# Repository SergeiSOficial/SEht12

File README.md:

# SEht12

That is 12 ethernet POE, I2C, CAN implementation. KiCAD source files

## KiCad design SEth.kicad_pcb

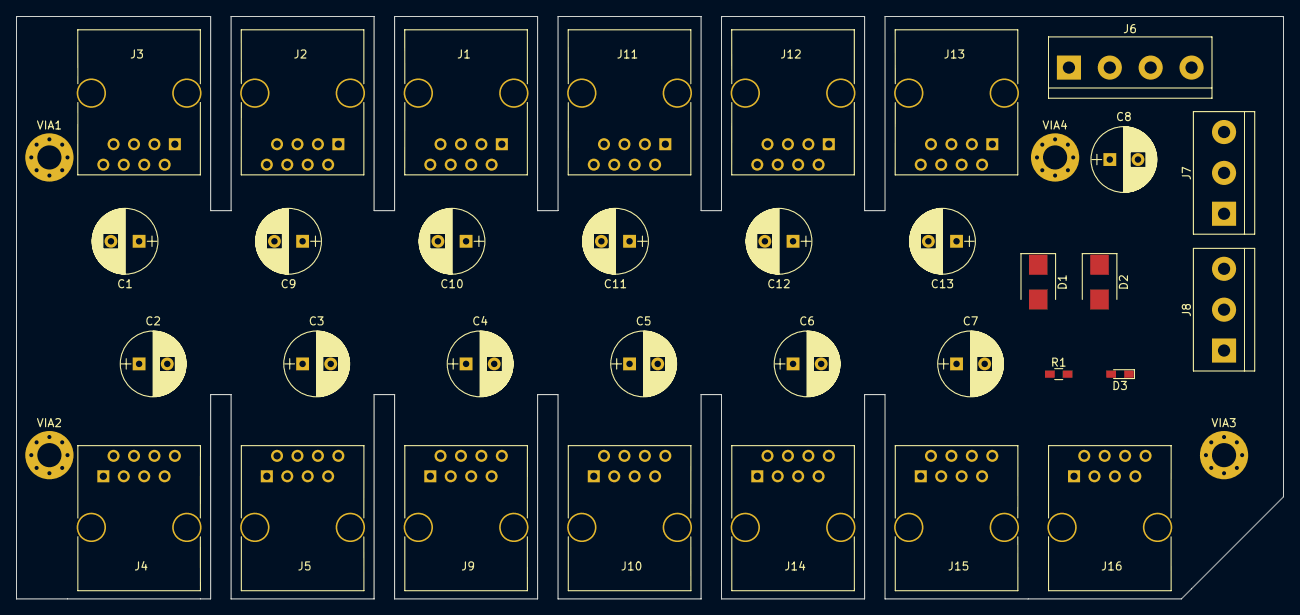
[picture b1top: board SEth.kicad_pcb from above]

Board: 2 copper layers, 157.5 x 72.4 mm, 37 parts (0 on the bottom side), 7 nets, no tracks yet.

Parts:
C1, C2, C3, C4, C5, C6, C7, C8, C9, C10, C11, C12, C13: CP; CP_Radial_D8.0mm_P3.50mm
D1: D_TVS; D_SMB
D2: D; D_SMB
D3: LED; LED_0603_HandSoldering
J1, J2, J3, J4, J5, J9, J10, J11, J12, J13, J14, J15, J16: RJ45; RJ45_8
J6: Screw_Terminal_01x04; TerminalBlock_bornier-4_P5.08mm
J7, J8: Screw_Terminal_01x03; TerminalBlock_bornier-3_P5.08mm
R1: 1K; R_0603_HandSoldering
VIA1, VIA2, VIA3, VIA4: 3mm_Pad_Via; MountingHole_3mm_Pad_Via

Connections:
+12V: C1.1, C2.1, C3.1, C4.1, C5.1, C6.1, C7.1, C8.1, C9.1, C10.1, C11.1, C12.1, C13.1, D1.1, D2.1, J1.4, J1.5, J2.4, J2.5, J3.4, J3.5, J4.4, J4.5, J5.4, J5.5, J6.1, J6.2, J9.4, J9.5, J10.4, J10.5, J11.4, J11.5, J12.4, J12.5, J13.4, J13.5, J14.4, J14.5, J15.4, J15.5, J16.4, J16.5, R1.1
CAN-H: J1.3, J2.3, J3.3, J4.3, J5.3, J8.1, J9.3, J10.3, J11.3, J12.3, J13.3, J14.3, J15.3, J16.3
CAN-L: J1.6, J2.6, J3.6, J4.6, J5.6, J8.2, J9.6, J10.6, J11.6, J12.6, J13.6, J14.6, J15.6, J16.6
GND: C1.2, C2.2, C3.2, C4.2, C5.2, C6.2, C7.2, C8.2, C9.2, C10.2, C11.2, C12.2, C13.2, D1.2, D2.2, D3.1, J1.7, J1.8, J1.9, J2.7, J2.8, J2.9, J3.7, J3.8, J3.9, J4.7, J4.8, J4.9, J5.7, J5.8, J5.9, J6.3, J6.4, J7.3, J8.3, J9.7, J9.8, J9.9, J10.7, J10.8, J10.9, J11.7, J11.8, J11.9, J12.7, J12.8, J12.9, J13.7, J13.8, J13.9, J14.7, J14.8, J14.9, J15.7, J15.8, J15.9, J16.7, J16.8, J16.9, VIA1.1, VIA2.1, VIA3.1, VIA4.1
unnamed: D3.2, R1.2
RS485_A: J1.1, J2.1, J3.1, J4.1, J5.1, J7.1, J9.1, J10.1, J11.1, J12.1, J13.1, J14.1, J15.1, J16.1
RS485_B: J1.2, J2.2, J3.2, J4.2, J5.2, J7.2, J9.2, J10.2, J11.2, J12.2, J13.2, J14.2, J15.2, J16.2

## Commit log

2018-05-01 Init project
